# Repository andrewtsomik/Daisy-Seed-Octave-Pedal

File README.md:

# Daisy Seed Octave Pedal

Using a Daisy Seed microcontroller, simulate an octave effects pedal for electric bass!
## Features

- **Sub octave** (-12 semitones) and **upper octave** (+12 semitones), each with its own level control
- **Envelope-gated** octave voices with hysteresis, so quiet passages and note decay don't produce gate chatter/zipper noise
- **Latching footswitch** one tap turns the effect on, another tap bypasses it
- Onboard LED tracks your playing envelope in real time
- True bypass fallback: bypassed signal is the untouched dry input
## Hardware
 
| Component        | Daisy Seed Pin | Purpose                     |
|------------------|:--------------:|------------------------------|
| Pot 1            | A0              | Dry level                   |
| Pot 2            | A1              | Sub-octave level             |
| Pot 3            | A2              | Upper-octave level           |
| Footswitch       | D18             | Effect on/off (momentary, wired to pull-up, active low) |
| LED              | D19             | Envelope indicator           |
| Input Jack       | A16             | Bass Input                   |
| Output Jack      | A18             | Amp Output                   |
| DC Jack          | A39             | Power Source                       |

## Schematic

## PCB Layout

## Fabricated and Assembled Design

### Front

### Back

### Assembled

## Demo (Don't hate I suck lol)

### Toggled On

https://github.com/user-attachments/assets/edada847-4ac4-451e-820c-bb3a319f9780

### Toggled Off

https://github.com/user-attachments/assets/274790b7-3237-4e18-9de3-0ea1d50deda9

## Flashing Instructions
Pre-Step 1
Run the commands below if you have not already cloned the libraries needed
```bash
git clone --recursive https://github.com/electro-smith/libDaisy.git
git clone --recursive https://github.com/electro-smith/DaisySP.git
```

1. Hold down the BOOT button your Daisy Seed
2. Press and release the RESET button
3. Release the BOOT button
4. Run the following command (Getting Error 74 is normal and a sign everything is working)

```bash
make clean && make && make program-dfu
```

5. Press and release the RESET button again

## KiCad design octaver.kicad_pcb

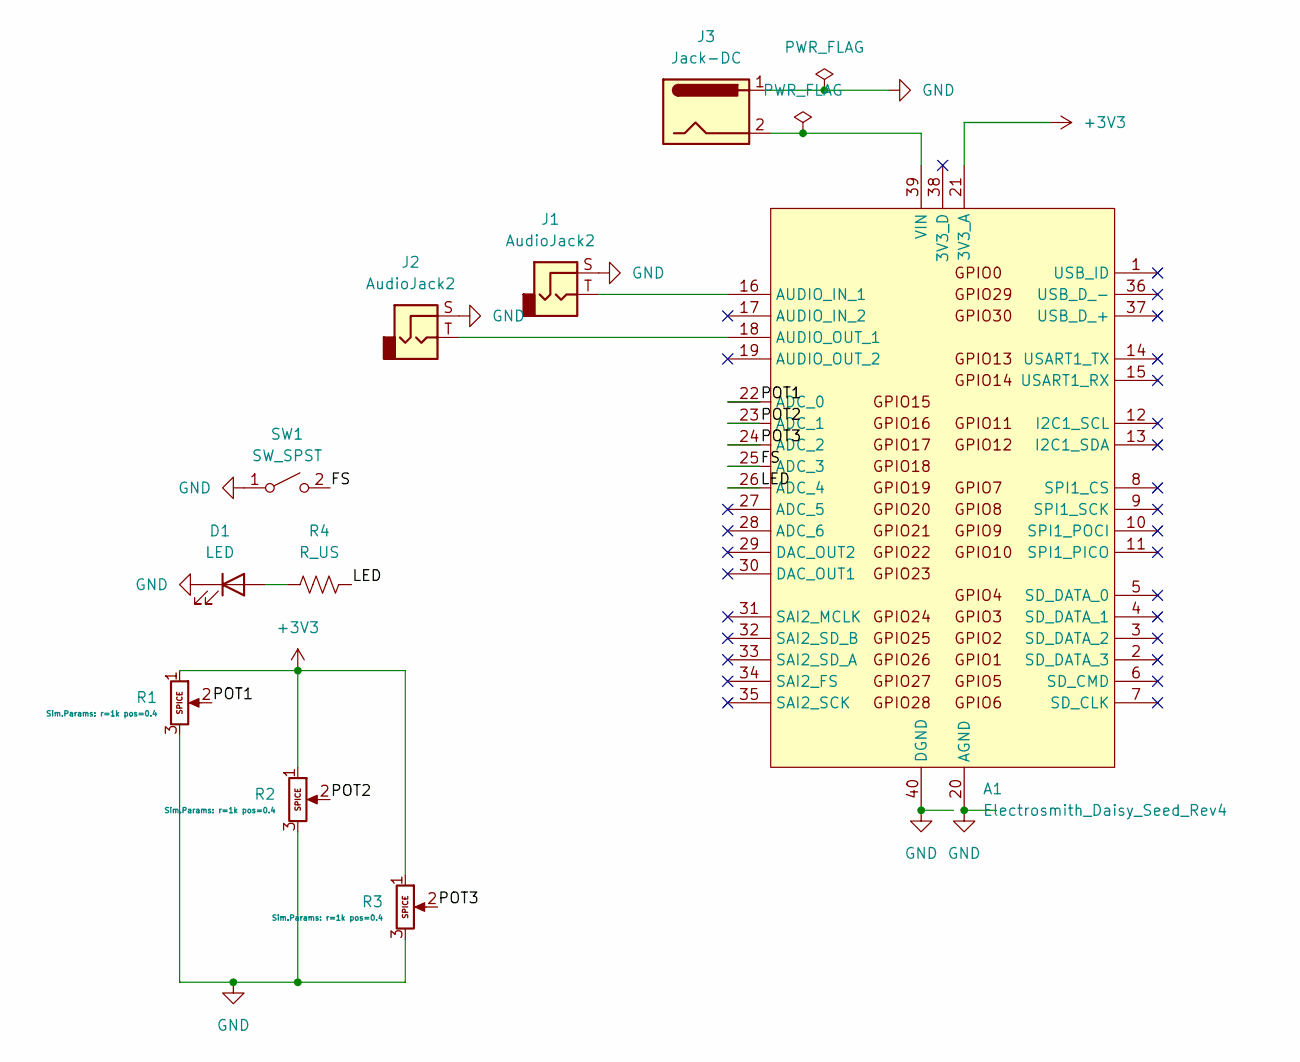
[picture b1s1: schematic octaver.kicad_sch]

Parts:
A1: Electrosmith_Daisy_Seed_Rev4; Electrosmith_Daisy_Seed
D1: LED; LED_D5.0mm
J1, J2: AudioJack2; SolderWire-0.5sqmm_1x02_P4.6mm_D0.9mm_OD2.1mm
J3: Jack-DC; SolderWire-0.5sqmm_1x02_P4.6mm_D0.9mm_OD2.1mm
R1, R2, R3: Potentiometer; Potentiometer_Alps_RK163_Single_Horizontal
R4: R_US; R_Axial_DIN0207_L6.3mm_D2.5mm_P7.62mm_Horizontal
SW1: SW_SPST; SolderWire-0.5sqmm_1x02_P4.6mm_D0.9mm_OD2.1mm

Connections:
+3V3: A1.21 (3V3_A), R1.1, R2.1, R3.1
/FS: A1.25 (ADC_3), SW1.2 (B)
/LED: A1.26 (ADC_4), R4.1
/POT1: A1.22 (ADC_0), R1.2
/POT2: A1.23 (ADC_1), R2.2
/POT3: A1.24 (ADC_2), R3.2
GND: A1.20 (AGND), A1.40 (DGND), D1.1 (K), J1.S, J2.S, J3.1, R1.3, R2.3, R3.3, SW1.1 (A)
unnamed: A1.16 (AUDIO_IN_1), J1.T
unnamed: A1.18 (AUDIO_OUT_1), J2.T
unnamed: A1.39 (VIN), J3.2
unnamed: D1.2 (A), R4.2

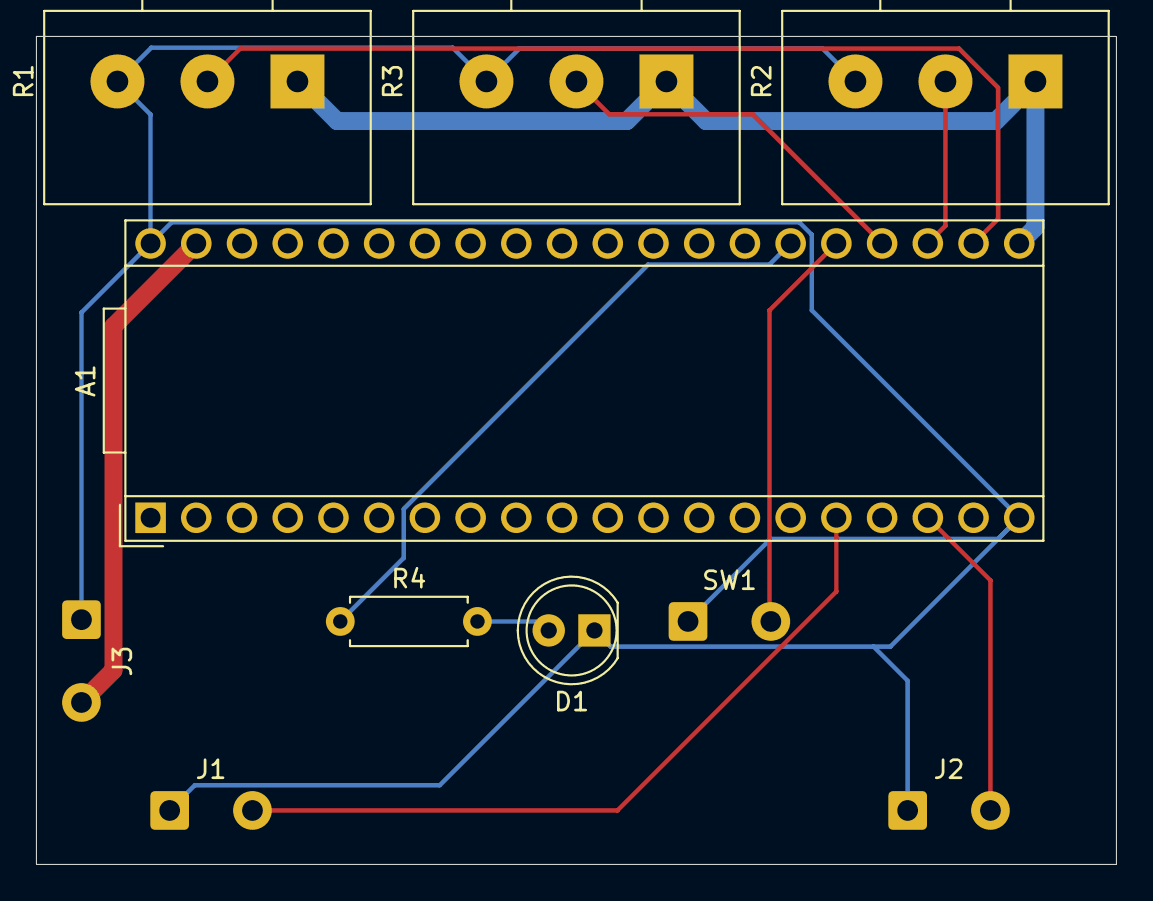
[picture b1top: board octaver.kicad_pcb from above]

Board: 2 copper layers, 60.0 x 46.0 mm, 10 parts (0 on the bottom side), 11 nets.

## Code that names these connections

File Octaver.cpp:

#include "daisy_seed.h"
#include "daisysp.h"
 
using namespace daisy;
using namespace daisy::seed;
using namespace daisysp;
 
#define POT1 A0
#define POT2 A1
#define POT3 A2
#define LED1  D19
#define FS_SWITCH  D18
 
enum AdcChannel
{
	PotOne,
	PotTwo,
	PotThree,
	NUM_ADC_CHANNELS
};
 
DaisySeed hw;
 
PitchShifter sub_shift;
PitchShifter upper_shift;
OnePole env_lpf;
Led led_gate;
Switch footswitch;
 
static constexpr float ENV_THRESHOLD_OPEN  = 0.01f;
static constexpr float ENV_THRESHOLD_CLOSE = 0.006f;
static constexpr float GATE_SMOOTH_COEFF   = 0.01f;
static constexpr float SMOOTH              = 0.002f;
 
float dry_smooth   = 0.7f;
float sub_smooth   = 0.8f;
float upper_smooth = 0.0f;
 
static bool  gate_state  = false;
static float gate_smooth = 0.0f;
 
static bool effect_on         = false;
static bool footswitch_last   = false;
 
void AudioCallback(AudioHandle::InputBuffer in, AudioHandle::OutputBuffer out, size_t size)
{
	bool footswitch_pressed = footswitch.Pressed();
	if(footswitch_pressed && !footswitch_last)
	{
		effect_on = !effect_on;
	}
	footswitch_last = footswitch_pressed;
 
	float pot_dry   = hw.adc.GetFloat(0);
	float pot_sub   = hw.adc.GetFloat(1);
	float pot_upper = hw.adc.GetFloat(2);
 
	dry_smooth   += SMOOTH * (pot_dry - dry_smooth);
	sub_smooth   += SMOOTH * (pot_sub - sub_smooth);
	upper_smooth += SMOOTH * (pot_upper - upper_smooth);
 
	for(size_t i = 0; i < size; i++)
	{
		float input = in[0][i];
 
		float rectified = fabsf(input);
		float envelope   = env_lpf.Process(rectified);
 
		if(!gate_state && envelope > ENV_THRESHOLD_OPEN)
		{
			gate_state = true;
		}
		else if(gate_state && envelope < ENV_THRESHOLD_CLOSE)
		{
			gate_state = false;
		}
 
		float gate_target = gate_state ? 1.0f : 0.0f;
		gate_smooth += GATE_SMOOTH_COEFF * (gate_target - gate_smooth);
 
		led_gate.Set(fclamp(envelope * 8.0f, 0.0f, 1.0f));
 
		float sub_out   = sub_shift.Process(input) * gate_smooth;
		float upper_out = upper_shift.Process(input) * gate_smooth;
 
		float mixed;
		if(effect_on)
		{
			mixed = input * dry_smooth + sub_out * sub_smooth + upper_out * upper_smooth;
			mixed = mixed / (1.0f + fabsf(mixed));
		}
		else
		{
			mixed = input;
		}
 
		out[0][i] = mixed;
		out[1][i] = mixed;
	}
}
 
int main(void)
{
	hw.Init();
	hw.SetAudioBlockSize(4);
	hw.SetAudioSampleRate(SaiHandle::Config::SampleRate::SAI_48KHZ);
 
	float sample_rate = hw.AudioSampleRate();
 
	AdcChannelConfig adc_cfg[NUM_ADC_CHANNELS];
	adc_cfg[PotOne].InitSingle(POT1);
	adc_cfg[PotTwo].InitSingle(POT2);
	adc_cfg[PotThree].InitSingle(POT3);
	hw.adc.Init(adc_cfg, NUM_ADC_CHANNELS);
	hw.adc.Start();
 
	sub_shift.Init(sample_rate);
	sub_shift.SetTransposition(-12.0f);
	sub_shift.SetFun(0.0f);
 
	upper_shift.Init(sample_rate);
	upper_shift.SetTransposition(12.0f);
	upper_shift.SetFun(0.0f);
 
	env_lpf.Init();
	env_lpf.SetFrequency(20.0f / sample_rate);
 
	led_gate.Init(LED1, false);
 
	footswitch.Init(FS_SWITCH, 1000.0f, Switch::TYPE_MOMENTARY, Switch::POLARITY_INVERTED, Switch::PULL_UP);
 
	hw.StartAudio(AudioCallback);
 
	while(1)
	{
		footswitch.Debounce();
		led_gate.Update();
		System::Delay(1);
	}
}
